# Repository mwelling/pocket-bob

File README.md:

# pocket-bob

Simple breakout board for the PocketBeagle line of products.

Provides pin headers for all of the pins and LEDs for all of the IOs and power outputs. Also breaks out USB host.

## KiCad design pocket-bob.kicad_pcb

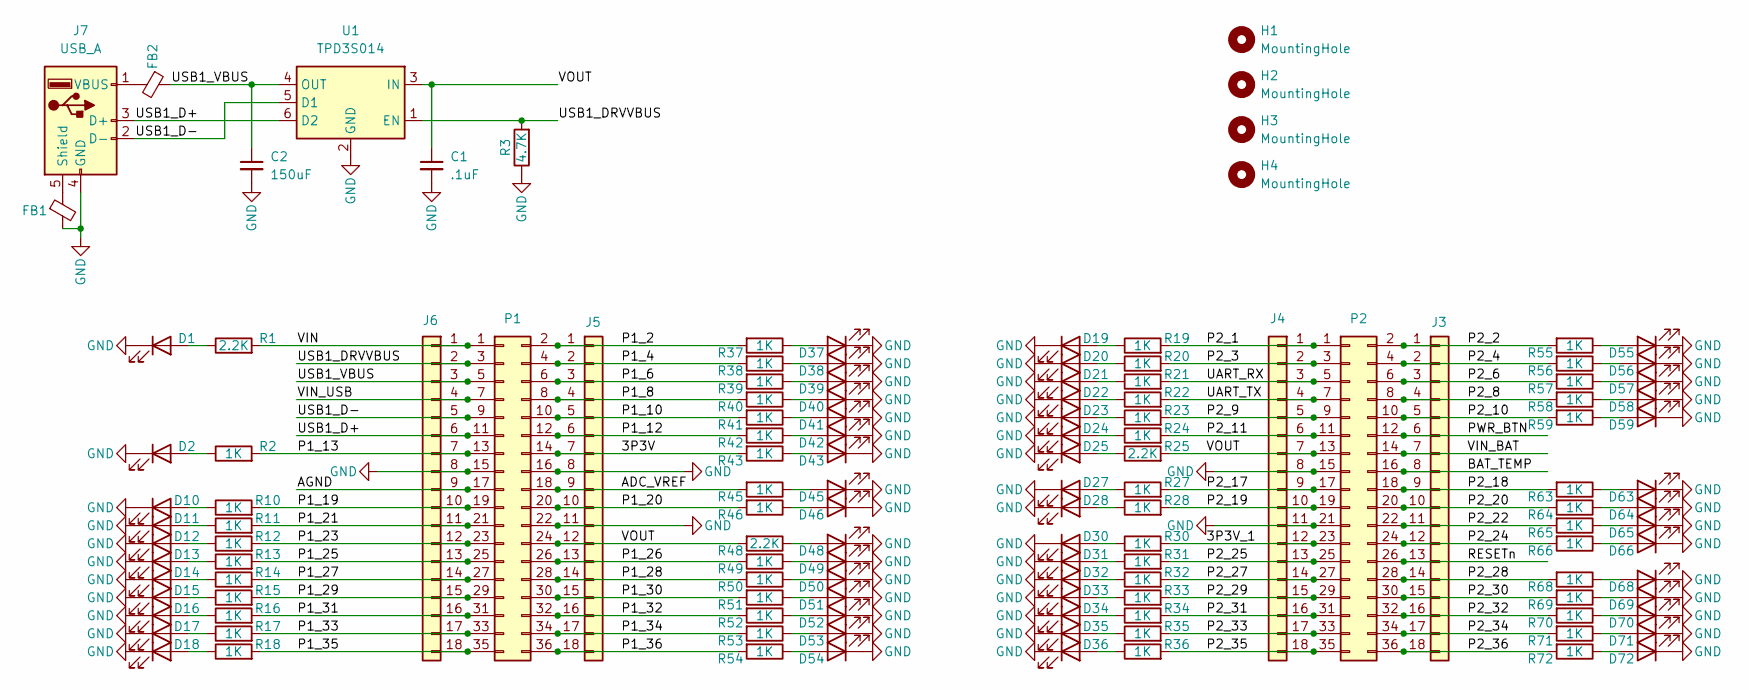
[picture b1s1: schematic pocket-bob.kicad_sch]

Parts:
C1: .1uF; C_0603_1608Metric
C2: 150uF; C_0603_1608Metric
D1, D25, D30, D43, D45, D48: RED; LED_0402_1005Metric
D2, D10, D11, D12, D13, D14, D15, D16, D17, D18, D19, D20, D21, D22, D23, D24, D27, D28, D31, D32, D33, D34, D35, D36, D37, D38, D39, D40, D41, D42, D46, D49, D50, D51, D52, D53, D54, D55, D56, D57, D58, D59, D63, D64, D65, D66, D68, D69, D70, D71, D72: GREEN; LED_0402_1005Metric
FB1, FB2: FerriteBead_Small; L_0603_1608Metric
H1, H2, H3, H4: MountingHole; MountingHole_2.7mm_M2.5
J3, J4, J5, J6: Conn_01x18; PinHeader_1x18_P2.54mm_Vertical
J7: USB_A; USB_A_Molex_67643_Horizontal
P1, P2: Conn_02x18_Odd_Even; PinHeader_2x18_P2.54mm_Vertical
R1, R25, R48: 2.2K; R_0402_1005Metric
R2, R10, R11, R12, R13, R14, R15, R16, R17, R18, R19, R20, R21, R22, R23, R24, R27, R28, R30, R31, R32, R33, R34, R35, R36, R37, R38, R39, R40, R41, R42, R43, R45, R46, R49, R50, R51, R52, R53, R54, R55, R56, R57, R58, R59, R63, R64, R65, R66, R68, R69, R70, R71, R72: 1K; R_0402_1005Metric
R3: 4.7K; R_0402_1005Metric
U1: TPD3S014; SOT-23-6

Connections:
/3P3V: J5.7, P1.14, R43.2
/3P3V_1: J4.12, P2.23, R30.2
/ADC_VREF: J5.9, P1.18, R45.2
/AGND: J6.9, P1.17
/BAT_TEMP: J3.8, P2.16
/P1_2: J5.1, P1.2, R37.2
/P1_4: J5.2, P1.4, R38.2
/P1_6: J5.3, P1.6, R39.2
/P1_8: J5.4, P1.8, R40.2
/P1_10: J5.5, P1.10, R41.2
/P1_12: J5.6, P1.12, R42.2
/P1_13: J6.7, P1.13, R2.2
/P1_19: J6.10, P1.19, R10.2
/P1_20: J5.10, P1.20, R46.2
/P1_21: J6.11, P1.21, R11.2
/P1_23: J6.12, P1.23, R12.2
/P1_25: J6.13, P1.25, R13.2
/P1_26: J5.13, P1.26, R49.2
/P1_27: J6.14, P1.27, R14.2
/P1_28: J5.14, P1.28, R50.2
/P1_29: J6.15, P1.29, R15.2
/P1_30: J5.15, P1.30, R51.2
/P1_31: J6.16, P1.31, R16.2
/P1_32: J5.16, P1.32, R52.2
/P1_33: J6.17, P1.33, R17.2
/P1_34: J5.17, P1.34, R53.2
/P1_35: J6.18, P1.35, R18.2
/P1_36: J5.18, P1.36, R54.2
/P2_1: J4.1, P2.1, R19.2
/P2_2: J3.1, P2.2, R55.2
/P2_3: J4.2, P2.3, R20.2
/P2_4: J3.2, P2.4, R56.2
/P2_6: J3.3, P2.6, R57.2
/P2_8: J3.4, P2.8, R58.2
/P2_9: J4.5, P2.9, R23.2
/P2_10: J3.5, P2.10, R59.2
/P2_11: J4.6, P2.11, R24.2
/P2_17: J4.9, P2.17, R27.2
/P2_18: J3.9, P2.18, R63.2
/P2_19: J4.10, P2.19, R28.2
/P2_20: J3.10, P2.20, R64.2
/P2_22: J3.11, P2.22, R65.2
/P2_24: J3.12, P2.24, R66.2
/P2_25: J4.13, P2.25, R31.2
/P2_27: J4.14, P2.27, R32.2
/P2_28: J3.14, P2.28, R68.2
/P2_29: J4.15, P2.29, R33.2
/P2_30: J3.15, P2.30, R69.2
/P2_31: J4.16, P2.31, R34.2
/P2_32: J3.16, P2.32, R70.2
/P2_33: J4.17, P2.33, R35.2
/P2_34: J3.17, P2.34, R71.2
/P2_35: J4.18, P2.35, R36.2
/P2_36: J3.18, P2.36, R72.2
/PWR_BTN: J3.6, P2.12
/RESETn: J3.13, P2.26
/UART_RX: J4.3, P2.5, R21.2
/UART_TX: J4.4, P2.7, R22.2
/USB1_D+: J6.6, J7.3 (D+), P1.11, U1.6 (D2)
/USB1_D-: J6.5, J7.2 (D-), P1.9, U1.5 (D1)
/USB1_DRVVBUS: J6.2, P1.3, R3.2, U1.1 (EN)
/USB1_VBUS: C2.1, FB2.1, J6.3, P1.5, U1.4 (OUT)
/VIN: J6.1, P1.1, R1.2
/VIN_BAT: J3.7, P2.14
/VIN_USB: J6.4, P1.7
/VOUT: C1.1, J4.7, J5.12, P1.24, P2.13, R25.2, R48.2, U1.3 (IN)
GND: C1.2, C2.2, D1.1 (K), D2.1 (K), D10.1 (K), D11.1 (K), D12.1 (K), D13.1 (K), D14.1 (K), D15.1 (K), D16.1 (K), D17.1 (K), D18.1 (K), D19.1 (K), D20.1 (K), D21.1 (K), D22.1 (K), D23.1 (K), D24.1 (K), D25.1 (K), D27.1 (K), D28.1 (K), D30.1 (K), D31.1 (K), D32.1 (K), D33.1 (K), D34.1 (K), D35.1 (K), D36.1 (K), D37.1 (K), D38.1 (K), D39.1 (K), D40.1 (K), D41.1 (K), D42.1 (K), D43.1 (K), D45.1 (K), D46.1 (K), D48.1 (K), D49.1 (K), D50.1 (K), D51.1 (K), D52.1 (K), D53.1 (K), D54.1 (K), D55.1 (K), D56.1 (K), D57.1 (K), D58.1 (K), D59.1 (K), D63.1 (K), D64.1 (K), D65.1 (K), D66.1 (K), D68.1 (K), D69.1 (K), D70.1 (K), D71.1 (K), D72.1 (K), FB1.2, J4.8, J4.11, J5.8, J5.11, J6.8, J7.4 (GND), P1.15, P1.16, P1.22, P2.15, P2.21, R3.1, U1.2 (GND)
unnamed: D1.2 (A), R1.1
unnamed: D2.2 (A), R2.1
unnamed: D10.2 (A), R10.1
unnamed: D11.2 (A), R11.1
unnamed: D12.2 (A), R12.1
unnamed: D13.2 (A), R13.1
unnamed: D14.2 (A), R14.1
unnamed: D15.2 (A), R15.1
unnamed: D16.2 (A), R16.1
unnamed: D17.2 (A), R17.1
unnamed: D18.2 (A), R18.1
unnamed: D19.2 (A), R19.1
unnamed: D20.2 (A), R20.1
unnamed: D21.2 (A), R21.1
unnamed: D22.2 (A), R22.1
unnamed: D23.2 (A), R23.1
unnamed: D24.2 (A), R24.1
unnamed: D25.2 (A), R25.1
unnamed: D27.2 (A), R27.1
unnamed: D28.2 (A), R28.1
unnamed: D30.2 (A), R30.1
unnamed: D31.2 (A), R31.1
unnamed: D32.2 (A), R32.1
unnamed: D33.2 (A), R33.1
unnamed: D34.2 (A), R34.1
unnamed: D35.2 (A), R35.1
unnamed: D36.2 (A), R36.1
unnamed: D37.2 (A), R37.1
unnamed: D38.2 (A), R38.1
unnamed: D39.2 (A), R39.1
unnamed: D40.2 (A), R40.1
unnamed: D41.2 (A), R41.1
unnamed: D42.2 (A), R42.1
unnamed: D43.2 (A), R43.1
unnamed: D45.2 (A), R45.1
unnamed: D46.2 (A), R46.1
unnamed: D48.2 (A), R48.1
unnamed: D49.2 (A), R49.1
unnamed: D50.2 (A), R50.1
unnamed: D51.2 (A), R51.1
unnamed: D52.2 (A), R52.1
unnamed: D53.2 (A), R53.1
unnamed: D54.2 (A), R54.1
unnamed: D55.2 (A), R55.1
unnamed: D56.2 (A), R56.1
unnamed: D57.2 (A), R57.1
unnamed: D58.2 (A), R58.1
unnamed: D59.2 (A), R59.1
unnamed: D63.2 (A), R63.1
unnamed: D64.2 (A), R64.1
unnamed: D65.2 (A), R65.1
unnamed: D66.2 (A), R66.1
unnamed: D68.2 (A), R68.1
unnamed: D69.2 (A), R69.1
unnamed: D70.2 (A), R70.1
unnamed: D71.2 (A), R71.1
unnamed: D72.2 (A), R72.1
unnamed: FB1.1, J7.5 (Shield)
unnamed: FB2.2, J7.1 (VBUS)

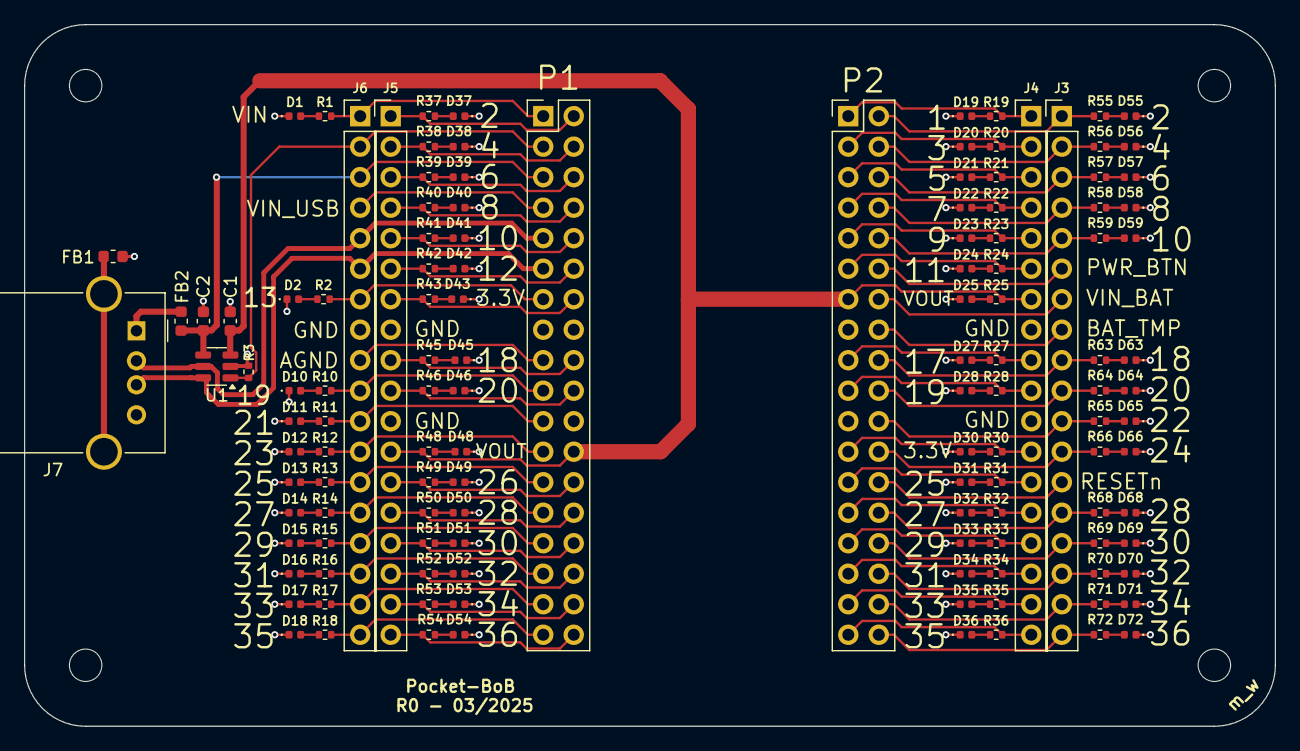
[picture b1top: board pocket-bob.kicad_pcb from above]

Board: 2 copper layers, 104.1 x 58.4 mm, 131 parts (0 on the bottom side), 126 nets.

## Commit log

2025-02-09 Initial push of pocket-bob
2025-02-09 Add schematic plot
2025-02-09 Add pin labels to silkscreen
2025-03-05 Clean up routing and add mounting holes to sch
2025-03-12 Update project to KiCAD 9
2025-03-12 Add image of board to README
2025-03-12 Remove tmp file
    Update gitignore.
2025-03-13 Some finishing touches
    Remove VIN_USB LED.
    Give resistors and LEDs some values.
    Update the pours.
    Update the silkscreen with board revision.
    Update all plots.
2025-03-13 Small updates
    Switched all 5V LED current limiting resistors to 2.2K.
2025-03-14 Switch P1_13 to LED instead of GND
    The USB_ID functionality is not need if we aren't using OTG.
2025-03-22 Update diff pairs
2025-04-11 design send out for fab
2025-04-17 Add digikey part number for components
